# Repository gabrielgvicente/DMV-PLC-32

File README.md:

# DMV-PLC-32
PLC usando ESP-32 de código aberto.

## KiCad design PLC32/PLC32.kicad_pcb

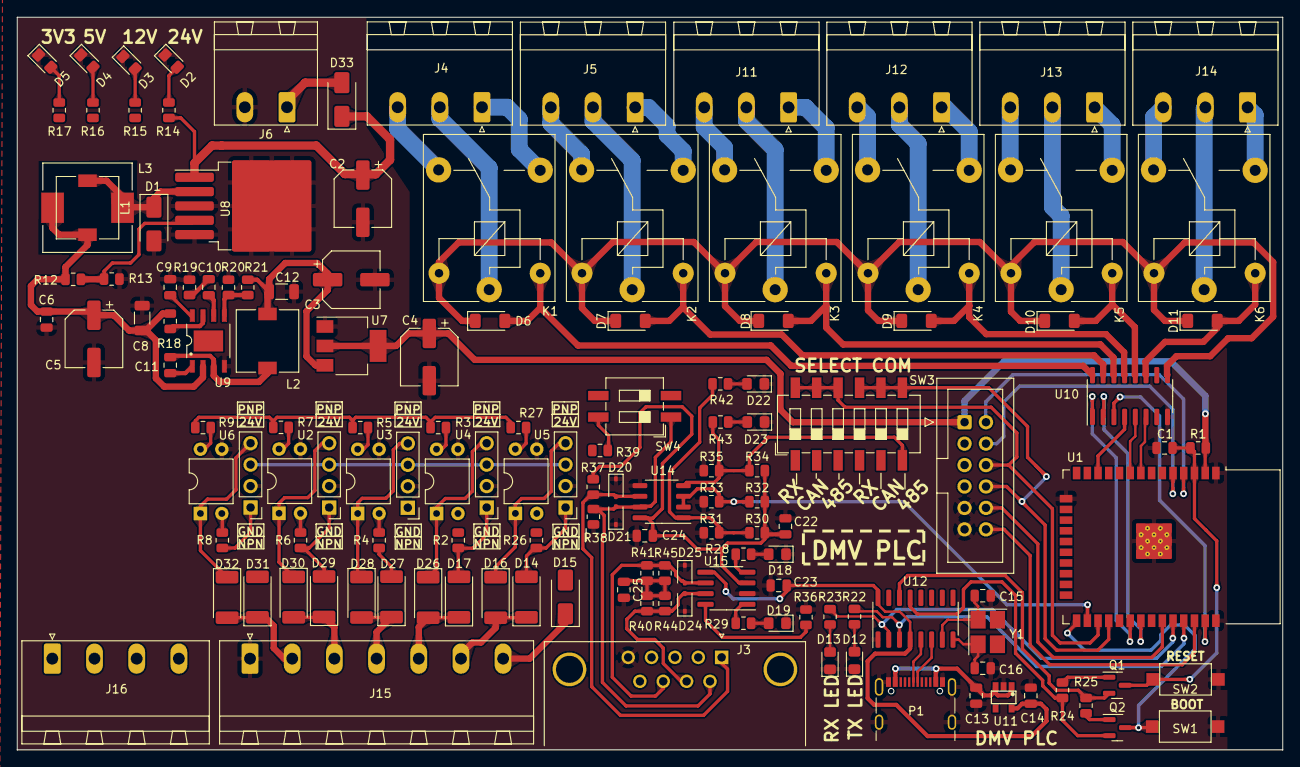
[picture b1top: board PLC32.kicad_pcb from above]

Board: 2 copper layers, 150.0 x 86.8 mm, 142 parts (0 on the bottom side), 113 nets.

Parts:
C1, C6, C22, C23: 100nF; C_0805_2012Metric
C2, C5: 220uF; CP_Elec_6.3x5.9
C3: 22OuF; CP_Elec_6.3x5.9
C4: 100uF; CP_Elec_6.3x5.9
C8: 4.7uF/25V; C_1206_3216Metric
C9: 0.1uF; C_0805_2012Metric
C10: 6.8nF; C_0805_2012Metric
C11: 10nF; C_0805_2012Metric
C12: 10uF/25V x2; C_1206_3216Metric
C13, C14, C24: 10uF; C_0805_2012Metric
C15, C16: 22pF; C_0805_2012Metric
C25: 4.7nF; C_0805_2012Metric
D1: IN5825; D_SMA
D2, D3, D4, D5, D12, D13, D18, D19, D22, D23: LED; LED_0805_2012Metric_Pad1.15x1.40mm_HandSolder
D6, D7, D8, D9, D10, D11: LL4148; D_MiniMELF
D14, D16, D17, D26, D27, D28, D29, D30, D31, D32: SM4007; D_MELF
D15, D33: 1N4007; D_SMA
D20, D21, D24, D25: SD15; D_SOD-323
J1: Conn_02x06_Odd_Even; IDC-Header_2x06_P2.54mm_Vertical
J2, J7, J8, J9, J10: Conn_01x04; PinHeader_1x04_P2.54mm_Vertical
J3: DB9_Female; DSUB-9_Female_Horizontal_P2.77x2.84mm_EdgePinOffset7.70mm_H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
J4, J5, J11, J12, J13, J14: Conn_01x03; PhoenixContact_MSTBA_2,5_3-G_1x03_P5.00mm_Horizontal
J6: Conn_01x02; PhoenixContact_MSTBA_2,5_2-G_1x02_P5.00mm_Horizontal
J15: Conn_01x07; PhoenixContact_MSTBA_2,5_7-G_1x07_P5.00mm_Horizontal
J16: Conn_01x04; PhoenixContact_MSTBA_2,5_4-G_1x04_P5.00mm_Horizontal
K1, K2, K3, K4, K5, K6: SANYOU_SRD_Form_C; Relay_SPDT_SANYOU_SRD_Series_Form_C
L1, L2: 10uH 4A; L_7.3x7.3_H3.5
L3: 10uH 4A; L_10.4x10.4_H4.8
P1: USB_C_Plug_USB2.0; USB_C_Receptacle_GCT_USB4105-xx-A_16P_TopMnt_Horizontal
Q1, Q2: BC847; SOT-23
R1, R3, R5, R7, R9, R12, R20, R27, R30, R31, R32, R33, R34, R35, R36: 10k; R_0805_2012Metric
R2, R4, R6, R8, R26: 1k2; R_0805_2012Metric
R13: 1.2k; R_0805_2012Metric
R14: 7.2k; R_0805_2012Metric
R15: 3.7k; R_0805_2012Metric
R16: 1,5k; R_0805_2012Metric
R17, R22, R23, R24, R25, R28, R29, R42, R43: 1k; R_0805_2012Metric
R18: 100k; R_0805_2012Metric
R19: 6.8k; R_0805_2012Metric
R21: 47k; R_0805_2012Metric
R37, R38: 20k; R_0805_2012Metric
R39, R40, R41, R44, R45: 120R; R_0805_2012Metric
SW1, SW2: SW_DIP_x01; SW_SPST_CK_RS282G05A3
SW3: SW_DIP_x04; SW_DIP_SPSTx06_Slide_6.7x16.8mm_W8.61mm_P2.54mm_LowProfile
SW4: SW_DIP_x02; SW_DIP_SPSTx02_Slide_6.7x6.64mm_W8.61mm_P2.54mm_LowProfile
U1: ESP32-WROOM-32
U2, U3, U4, U5, U6: PC817; DIP-4_W7.62mm
U7: AMS1117-3.3; SOT-223-3_TabPin2
U8: LM2596S-ADJ; TO-263-5_TabPin3
U9: MP1484; SOP127P600X175-9N
U10: ULN2003A; SOIC-16_3.9x9.9mm_P1.27mm
U11: RT9193-33GB; Richtek-RT9193-33GB-0
U12: CH340G; SOIC-16_3.9x9.9mm_P1.27mm
U14: MAX485E; SO-8_3.9x4.9mm_P1.27mm
U15: TJA1049T-3; SOIC-8_3.9x4.9mm_P1.27mm
Y1: 12MHZ; Crystal_SMD_3225-4Pin_3.2x2.5mm_HandSoldering

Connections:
+3.3V: R3.2, R5.2, R7.2, R9.2, R27.2
+3V3: C4.1, C14.1, C23.1, J1.1, R1.2, R17.2, U1.2 (VDD), U7.2 (VO), U11.5 (VOUT), U12.4 (V3), U12.16 (VCC), U15.5 (VIO)
+5V: C3.1, C12.1, C22.1, C24.1, J1.3, L2.2, R16.2, R21.1, R30.2, R32.2, R34.2, R37.2, U7.3 (VI), U14.8 (VCC), U15.3 (VCC)
+12V: C5.1, C6.1, C8.1, D6.1 (K), D7.1 (K), D8.1 (K), D9.1 (K), D10.1 (K), D11.1 (K), J1.5, K1.5, K2.5, K3.5, K4.5, K5.5, K6.5, L1.2, L3.2, R12.2, R15.2, R18.1, U9.2 (IN), U10.9 (COM)
+24V: C2.1, D15.2 (A), D33.1 (K), J1.7, J2.3, J7.3, J8.3, J9.3, J10.3, R14.2, U8.1 (VIN)
/AUX1: J1.2, U1.4 (SENSOR_VP)
/AUX2: J1.4, U1.5 (SENSOR_VN)
/BOOT: Q2.3 (C), SW1.1, U1.25 (IO0)
/COMUNICAÇÃO/A_RS485: D20.2 (A2), J3.1, R37.1, R39.2, U14.6 (A)
/COMUNICAÇÃO/B_RS485: D21.2 (A2), J3.6, R38.2, SW4.1, U14.7 (B)
/COMUNICAÇÃO/CAN_H: D24.2 (A2), J3.7, R40.1, R44.1, U15.7 (CANH)
/COMUNICAÇÃO/CAN_L: D25.2 (A2), J3.8, R41.2, R45.2, U15.6 (CANL)
/COMUNICAÇÃO/RX_CAN: R28.2, SW3.5, U15.4 (RXD)
/COMUNICAÇÃO/RX_RS485: R34.1, R35.2, R43.2, SW3.6, U14.4 (DI)
/COMUNICAÇÃO/TX_CAN: R29.2, SW3.2, U15.1 (TXD)
/COMUNICAÇÃO/TX_RS485: R30.1, R31.2, R42.2, SW3.3, U14.1 (RO)
/EN: C1.1, Q1.3 (C), R1.1, SW2.1, U1.3 (EN)
/EN_CAN: R36.2, U1.16 (IO13), U15.8 (STB)
/INPUTS/+24V_IN: D15.1 (K), J15.7
/INPUTS/IN1: D14.1 (K), D16.2 (A), J15.6
/INPUTS/IN2: D17.1 (K), D26.2 (A), J15.5
/INPUTS/IN3: D27.1 (K), D28.2 (A), J15.4
/INPUTS/IN4: D29.1 (K), D30.2 (A), J15.3
/INPUTS/IN5: D31.1 (K), D32.2 (A), J15.2
/MIC_IN1: R27.1, U1.24 (IO2), U5.4
/MIC_IN2: R3.1, U1.29 (IO5), U4.4
/MIC_IN3: R5.1, U1.14 (IO12), U3.4
/MIC_IN4: R7.1, U1.13 (IO14), U2.4
/MIC_IN5: R9.1, U1.23 (IO15), U6.4
/MIC_OUT1: U1.30 (IO18), U10.1 (I1)
/MIC_OUT2: U1.31 (IO19), U10.2 (I2)
/MIC_OUT3: U1.37 (IO23), U10.3 (I3)
/MIC_OUT4: U1.12 (IO27), U10.4 (I4)
/MIC_OUT5: U1.9 (IO33), U10.5 (I5)
/MIC_OUT6: U1.8 (IO32), U10.6 (I6)
/OUTPUTS/COM_OUT1: J4.2, K1.1
/OUTPUTS/COM_OUT2: J5.2, K2.1
/OUTPUTS/COM_OUT3: J11.2, K3.1
/OUTPUTS/COM_OUT4: J12.2, K4.1
/OUTPUTS/COM_OUT5: J13.2, K5.1
/OUTPUTS/COM_OUT6: J14.2, K6.1
/OUTPUTS/NA1: J4.1, K1.3
/OUTPUTS/NA2: J5.1, K2.3
/OUTPUTS/NA3: J11.1, K3.3
/OUTPUTS/NA4: J12.1, K4.3
/OUTPUTS/NA5: J13.1, K5.3
/OUTPUTS/NA6: J14.1, K6.3
/OUTPUTS/NF1: J4.3, K1.4
/OUTPUTS/NF2: J5.3, K2.4
/OUTPUTS/NF3: J11.3, K3.4
/OUTPUTS/NF4: J12.3, K4.4
/OUTPUTS/NF5: J13.3, K5.4
/OUTPUTS/NF6: J14.3, K6.4
/RTS: R32.1, R33.2, U1.26 (IO4), U14.2 (~RE), U14.3 (DE)
/RX_UART0: R23.2, U1.34 (RXD0/IO3), U12.2 (TXD)
/RX_UART2: J1.6, SW3.10, SW3.11, SW3.12, U1.27 (IO16)
/SCL: J1.12, U1.36 (IO22)
/SDA: J1.10, U1.33 (IO21)
/TX_UART0: R22.2, U1.35 (TXD0/IO1), U12.3 (RXD)
/TX_UART2: J1.8, SW3.7, SW3.8, SW3.9, U1.28 (IO17)
/USB/DTR: Q2.2 (E), R24.2, U12.13 (~DTR)
/USB/RTS: Q1.2 (E), R25.2, U12.14 (~RTS)
/USB/VBUS: C13.1, P1.A4 (VBUS), P1.A9 (VBUS), P1.B4 (VBUS), P1.B9 (VBUS), U11.1 (VIN), U11.3 (EN)
GND: C1.2, C2.2, C3.2, C4.2, C5.2, C6.2, C8.2, C9.2, C12.2, C13.2, C14.2, C15.2, C16.2, C22.2, C23.2, C24.2, C25.2, D1.2 (A), D2.1 (K), D3.1 (K), D4.1 (K), D5.1 (K), D12.1 (K), D13.1 (K), D18.1 (K), D19.1 (K), D20.1 (A1), D21.1 (A1), D22.1 (K), D23.1 (K), D24.1 (A1), D25.1 (A1), J1.9, J1.11, J2.2, J3.5, J6.2, J7.2, J8.2, J9.2, J10.2, J15.1, P1.A1 (GND), P1.A12 (GND), P1.B1 (GND), P1.B12 (GND), P1.S1 (SHIELD), R13.2, R19.2, R20.2, R31.1, R33.1, R35.1, R36.1, R38.1, SW1.2, SW2.2, U1.1 (GND), U1.15 (GND), U1.38 (GND), U1.39 (GND), U2.3, U3.3, U4.3, U5.3, U6.3, U7.1 (GND), U8.3 (GND), U8.5 (~ON/OFF), U9.4 (GND), U10.8 (GND), U11.2 (GND), U12.1 (GND), U14.5 (GND), U15.2 (GND)
unnamed: C10.2, R19.1
unnamed: C25.1, R40.2, R41.1, R44.2, R45.1
unnamed: D1.1 (K), L1.1, L3.1, U8.2 (OUT)
unnamed: D2.2 (A), R14.1
unnamed: D3.2 (A), R15.1
unnamed: D4.2 (A), R16.1
unnamed: D5.2 (A), R17.1
unnamed: D6.2 (A), K1.2, U10.16 (O1)
unnamed: D7.2 (A), K2.2, U10.15 (O2)
unnamed: D8.2 (A), K3.2, U10.14 (O3)
unnamed: D9.2 (A), K4.2, U10.13 (O4)
unnamed: D10.2 (A), K5.2, U10.12 (O5)
unnamed: D11.2 (A), K6.2, U10.11 (O6)
unnamed: D12.2 (A), R22.1
unnamed: D13.2 (A), R23.1
unnamed: D14.2 (A), J2.1, R26.1
unnamed: D16.1 (K), J2.4, U5.1
unnamed: D17.2 (A), J7.1, R2.1
unnamed: D18.2 (A), R28.1
unnamed: D19.2 (A), R29.1
unnamed: D22.2 (A), R42.1
unnamed: D23.2 (A), R43.1
unnamed: D26.1 (K), J7.4, U4.1
unnamed: D27.2 (A), J8.1, R4.1
unnamed: D28.1 (K), J8.4, U3.1
unnamed: D29.2 (A), J9.1, R6.1
unnamed: D30.1 (K), J9.4, U2.1
unnamed: D31.2 (A), J10.1, R8.1
unnamed: D32.1 (K), J10.4, U6.1
unnamed: D33.2 (A), J6.1
unnamed: P1.A6 (D+), U12.5 (UD+)
unnamed: P1.A7 (D-), U12.6 (UD-)
unnamed: Q1.1 (B), R24.1
unnamed: Q2.1 (B), R25.1
unnamed: R2.2, U4.2
unnamed: R4.2, U3.2
unnamed: R6.2, U2.2
unnamed: R8.2, U6.2
unnamed: R26.2, U5.2
unnamed: R39.1, SW4.4
unnamed: R12.1, R13.1, U8.4 (FB)
unnamed: C11.1, U9.1 (BS)
unnamed: C10.1, U9.6 (COMP)
unnamed: R18.2, U9.7 (EN)
unnamed: R20.1, R21.2, U9.5 (FB)
unnamed: C9.1, U9.8 (SS)
unnamed: C11.2, L2.1, U9.3 (SW)
unnamed: C15.1, U12.7 (XI), Y1.1
unnamed: C16.1, U12.8 (XO), Y1.2

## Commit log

2023-04-11 alterado diodo de alimentação das entradas digitais
2023-04-11 adicionado diodo de alimentação das entradas digitais
